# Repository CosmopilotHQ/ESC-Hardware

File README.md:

<p align="center">

</p>

# Brushed Speed Controller

This project aims to create a Brushed Electronic Speed Controller (ESC) using KiCad. The ESC is designed to control the speed of a brushed DC motor using pulse-width modulation (PWM) signals.

## Getting Started

To get started with this project, follow these steps:

1. Clone this repository to your local machine.
   ```bash
   git clone https://github.com/CosmopilotHQ/ESC-Hardware.git
   ```

## Port Manipulation

Port manipulation is a method used to directly control the state of GPIO (General Purpose Input/Output). Instead of using digitalWrite() and digitalRead() functions, which are higher-level abstractions, port manipulation accesses the hardware registers directly.

### Clearing a Bit in a Register

To clear a bit in a register, you typically perform a bitwise AND operation between the register and the complement of a bitmask that has the desired bit set.

```c
register &= ~(1 << bit_position);
```

### Setting a Bit in a Register

To set a bit in a register, you typically perform a bitwise OR operation between the register and a bitmask that has the desired bit set.

```c
register |= (1 << bit_position);
```

### Example

- Setting Pin as Output

  ```C
  DDRD |= (1 << PD5);
  ```

- Turning Pin High

  ```c
  PORTB |= (1 << PD5);
  ```

- Turning Pin Low
  ```c
  PORTB &= ~(1 << PD5);
  ```

## License

This project is licensed under CERN Open Hardware License. You can find more details in the [LICENSE](LICENSE) file.

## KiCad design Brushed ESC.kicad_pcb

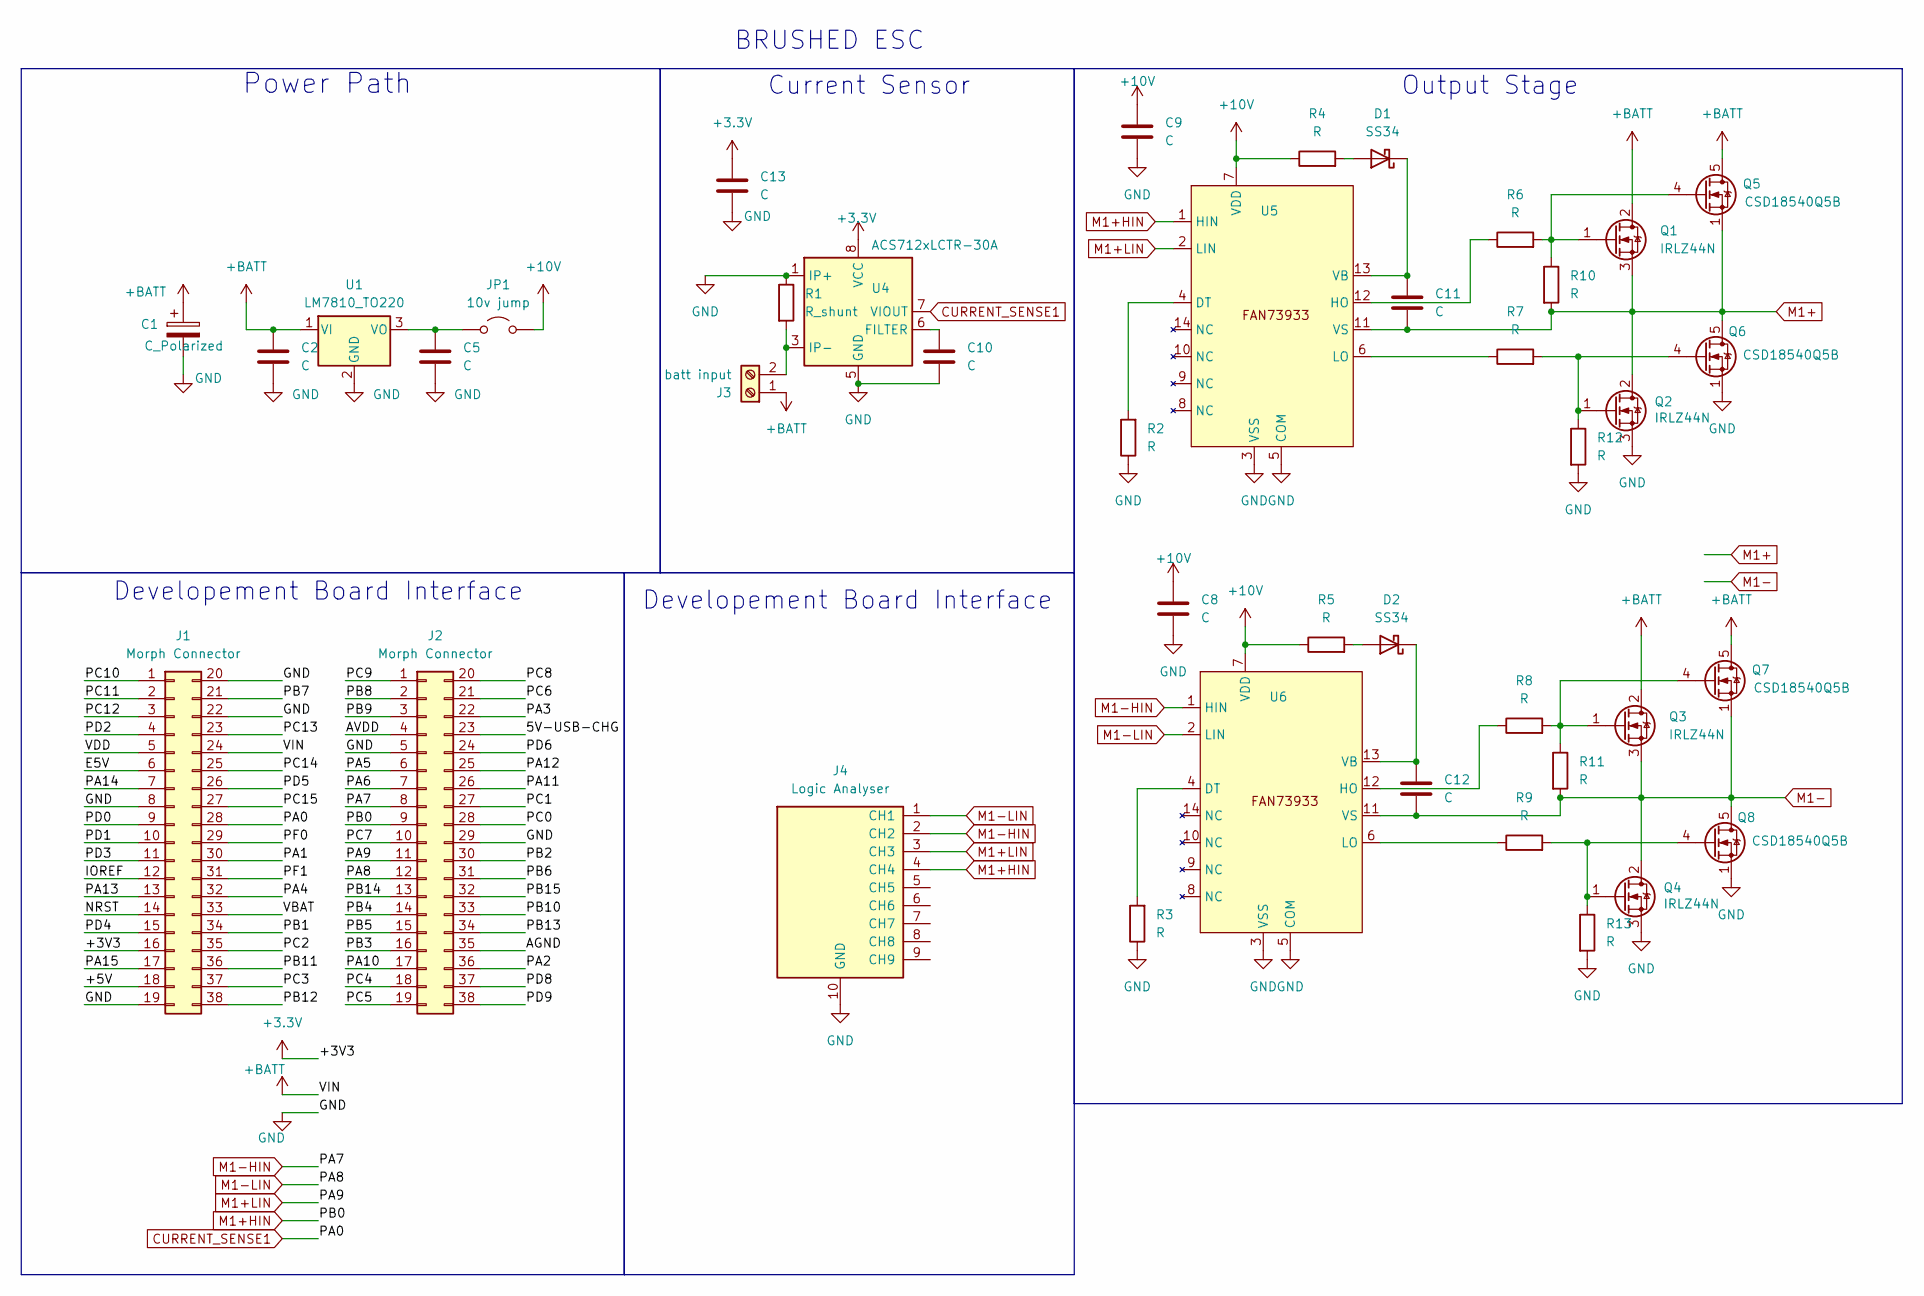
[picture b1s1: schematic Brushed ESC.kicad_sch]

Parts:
C1: C_Polarized; CP_Radial_D8.0mm_P5.00mm
C2, C5: C; C_1825_4564Metric_Pad1.57x6.80mm_HandSolder
C8, C9, C10, C11, C12: C; C_1206_3216Metric_Pad1.33x1.80mm_HandSolder
C13: C; C_1210_3225Metric_Pad1.33x2.70mm_HandSolder
D1, D2: SS34; D_SMA
J1, J2: Morph Connector; PinHeader_2x19_P2.54mm_Vertical
J3: batt input; JST_NV_B02P-NV_1x02_P5.00mm_Vertical
J4: Logic Analyser; IDC-Header_2x05_P2.54mm_Vertical
JP1: 10v jump; SolderJumper-2_P1.3mm_Open_TrianglePad1.0x1.5mm
Q1, Q2, Q3, Q4: IRLZ44N; TO-220-3_Vertical
Q5, Q6, Q7, Q8: CSD18540Q5B; Infineon_PG-TDSON-8_6.15x5.15mm
R1: R_shunt; R_2816_7142Metric_Pad3.20x4.45mm_HandSolder
R2, R3, R4, R5, R6, R7, R8, R9, R10, R11, R12, R13: R; R_1206_3216Metric_Pad1.30x1.75mm_HandSolder
U1: LM7810_TO220; TO-220-3_Vertical
U4: ACS712xLCTR-30A; SOIC-8_3.9x4.9mm_P1.27mm
U5, U6: SOIC-14_3.9x8.7mm_P1.27mm

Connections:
+3.3V: C13.1, J1.16, U4.8 (VCC)
+10V: C8.1, C9.1, JP1.2 (B), R4.1, R5.1, U5.7 (VDD), U6.7 (VDD)
+BATT: C1.1, C2.1, J1.24, J3.1, Q1.2 (D), Q3.2 (D), Q5.5 (D), Q7.5 (D), U1.1 (VI)
/5V-USB-CHG: J2.23
/+5V: J1.18
/AGND: J2.35
/AVDD: J2.4
/E5V: J1.6
/IOREF: J1.12
/NRST: J1.14
/PA1: J1.30
/PA2: J2.36
/PA3: J2.22
/PA4: J1.32
/PA5: J2.6
/PA6: J2.7
/PA10: J2.17
/PA11: J2.26
/PA12: J2.25
/PA13: J1.13
/PA14: J1.7
/PA15: J1.17
/PB1: J1.34
/PB2: J2.30
/PB3: J2.16
/PB4: J2.14
/PB5: J2.15
/PB6: J2.31
/PB7: J1.21
/PB8: J2.2
/PB9: J2.3
/PB10: J2.33
/PB11: J1.36
/PB12: J1.38
/PB13: J2.34
/PB14: J2.13
/PB15: J2.32
/PC0: J2.28
/PC1: J2.27
/PC2: J1.35
/PC3: J1.37
/PC4: J2.18
/PC5: J2.19
/PC6: J2.21
/PC7: J2.10
/PC8: J2.20
/PC9: J2.1
/PC10: J1.1
/PC11: J1.2
/PC12: J1.3
/PC13: J1.23
/PC14: J1.25
/PC15: J1.27
/PD0: J1.9
/PD1: J1.10
/PD2: J1.4
/PD3: J1.11
/PD4: J1.15
/PD5: J1.26
/PD6: J2.24
/PD8: J2.37
/PD9: J2.38
/PF0: J1.29
/PF1: J1.31
/VBAT: J1.33
/VDD: J1.5
CURRENT_SENSE1: J1.28, U4.7 (VIOUT)
GND: C1.2, C2.2, C5.2, C8.2, C9.2, C10.2, C13.2, J1.8, J1.19, J1.20, J1.22, J2.5, J2.29, J4.10 (GND), Q2.3 (S), Q4.3 (S), Q6.1 (S), Q6.2 (S), Q6.3 (S), Q8.1 (S), Q8.2 (S), Q8.3 (S), R1.1, R2.1, R3.1, R12.2, R13.2, U1.2 (GND), U4.1 (IP+), U4.2 (IP+), U4.5 (GND), U5.3 (VSS), U5.5 (COM), U6.3 (VSS), U6.5 (COM)
M1+: C11.2, Q1.3 (S), Q2.2 (D), Q5.1 (S), Q5.2 (S), Q5.3 (S), Q6.5 (D), R10.2, U5.11 (VS)
M1+HIN: J2.9, J4.4 (CH4), U5.1 (HIN)
M1+LIN: J2.11, J4.3 (CH3), U5.2 (LIN)
M1-: C12.2, Q3.3 (S), Q4.2 (D), Q7.1 (S), Q7.2 (S), Q7.3 (S), Q8.5 (D), R11.2, U6.11 (VS)
M1-HIN: J2.8, J4.2 (CH2), U6.1 (HIN)
M1-LIN: J2.12, J4.1 (CH1), U6.2 (LIN)
unnamed: D1.2 (A), R4.2
unnamed: C11.1, D1.1 (K), U5.13 (VB)
unnamed: D2.2 (A), R5.2
unnamed: C12.1, D2.1 (K), U6.13 (VB)
unnamed: J3.2, R1.2, U4.3 (IP-), U4.4 (IP-)
unnamed: C5.1, JP1.1 (A), U1.3 (VO)
unnamed: Q1.1 (G), Q5.4 (G), R6.2, R10.1
unnamed: Q2.1 (G), Q6.4 (G), R7.2, R12.1
unnamed: Q3.1 (G), Q7.4 (G), R8.2, R11.1
unnamed: Q4.1 (G), Q8.4 (G), R9.2, R13.1
unnamed: C10.1, U4.6 (FILTER)
unnamed: R2.2, U5.4 (DT)
unnamed: R6.1, U5.12 (HO)
unnamed: R7.1, U5.6 (LO)
unnamed: R3.2, U6.4 (DT)
unnamed: R8.1, U6.12 (HO)
unnamed: R9.1, U6.6 (LO)

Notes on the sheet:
BRUSHED ESC
Developement Board Interface
Output Stage
Power Path
Current Sensor

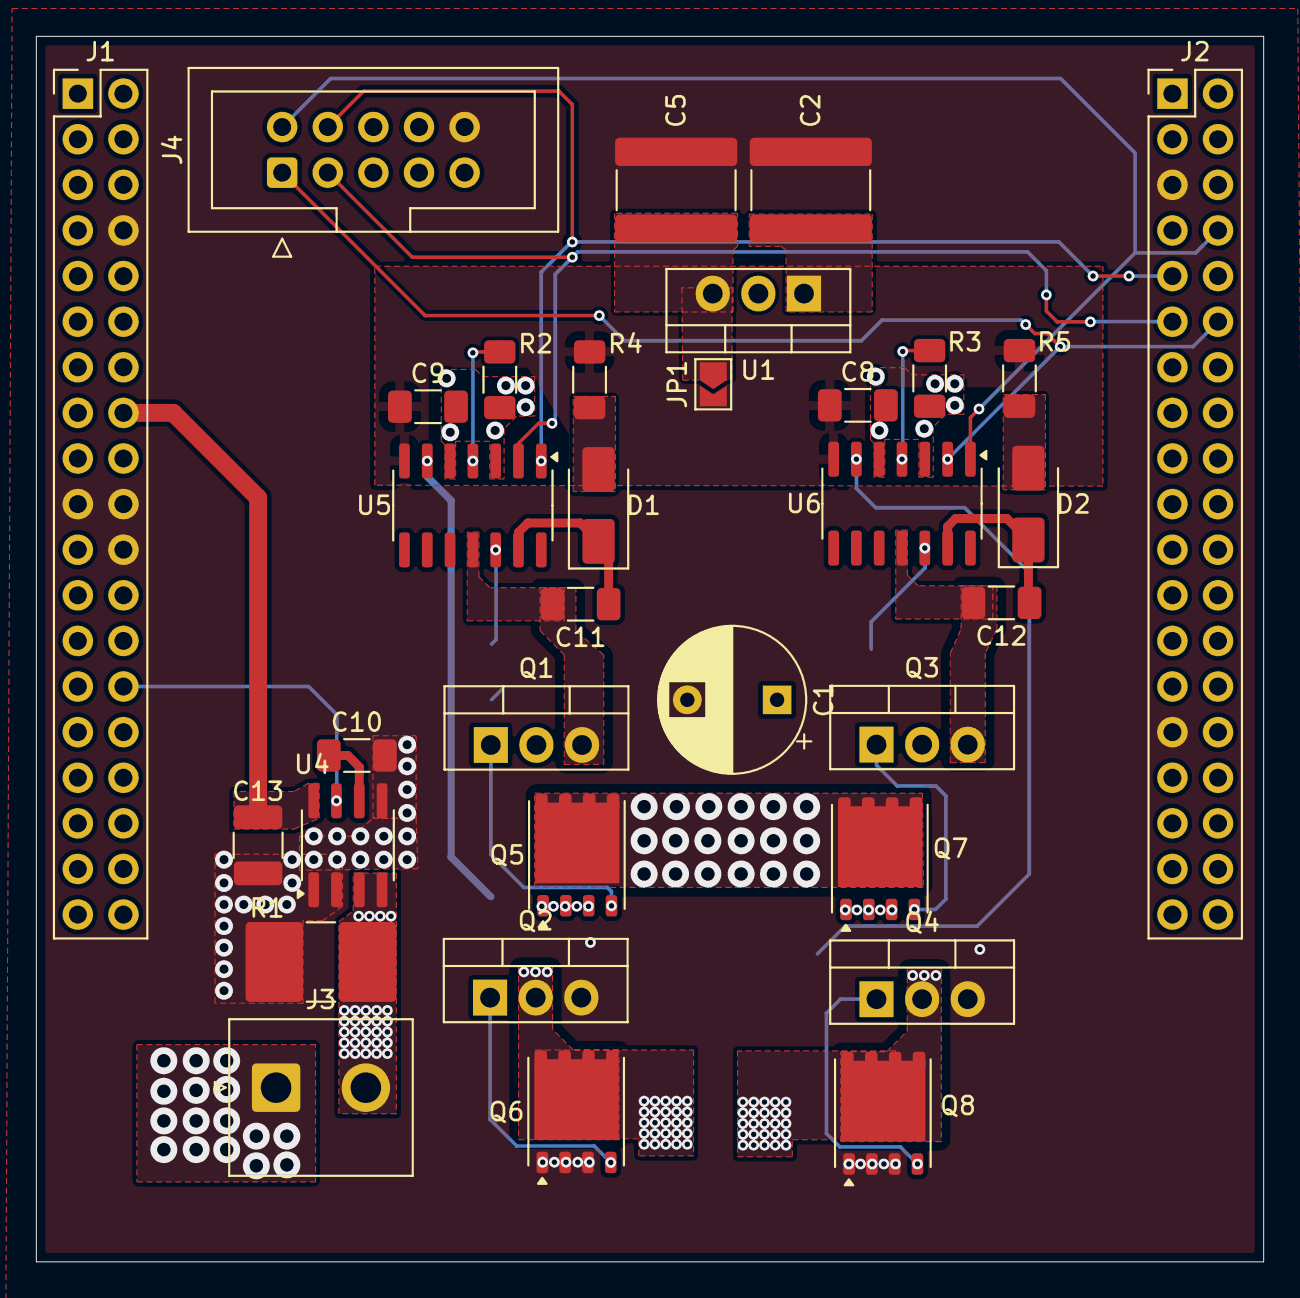
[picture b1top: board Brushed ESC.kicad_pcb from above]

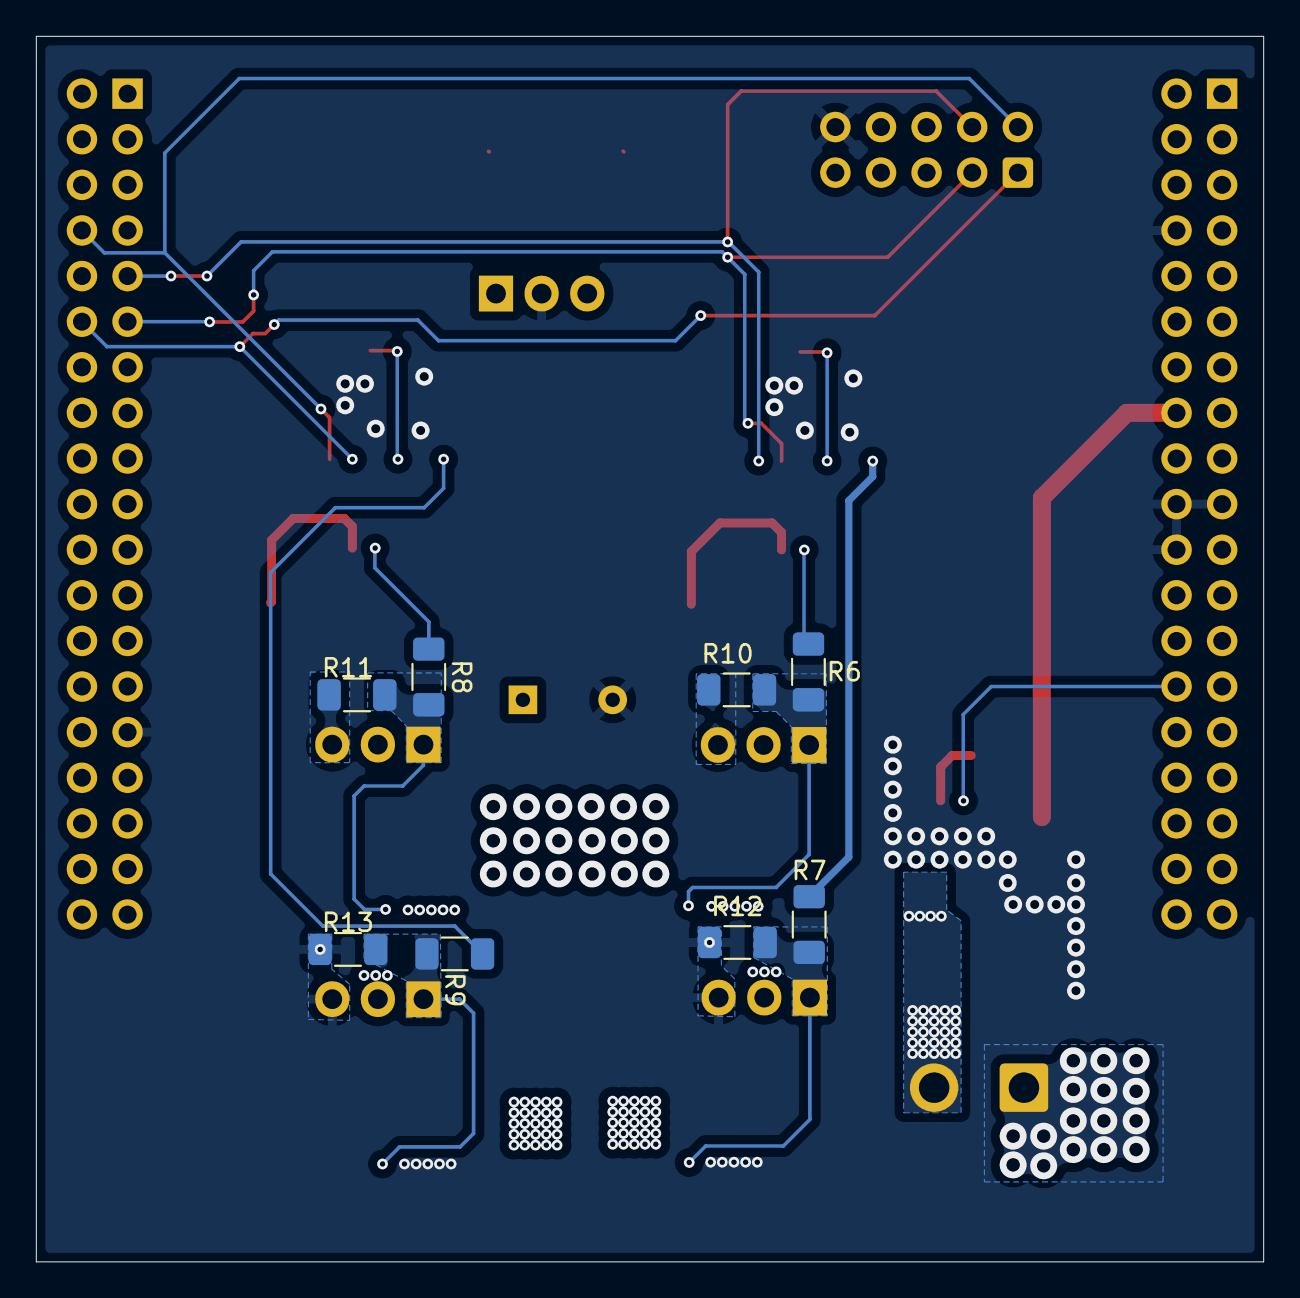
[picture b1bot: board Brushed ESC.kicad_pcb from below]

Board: 4 copper layers, 68.3 x 68.2 mm, 41 parts (8 on the bottom side), 28 nets.

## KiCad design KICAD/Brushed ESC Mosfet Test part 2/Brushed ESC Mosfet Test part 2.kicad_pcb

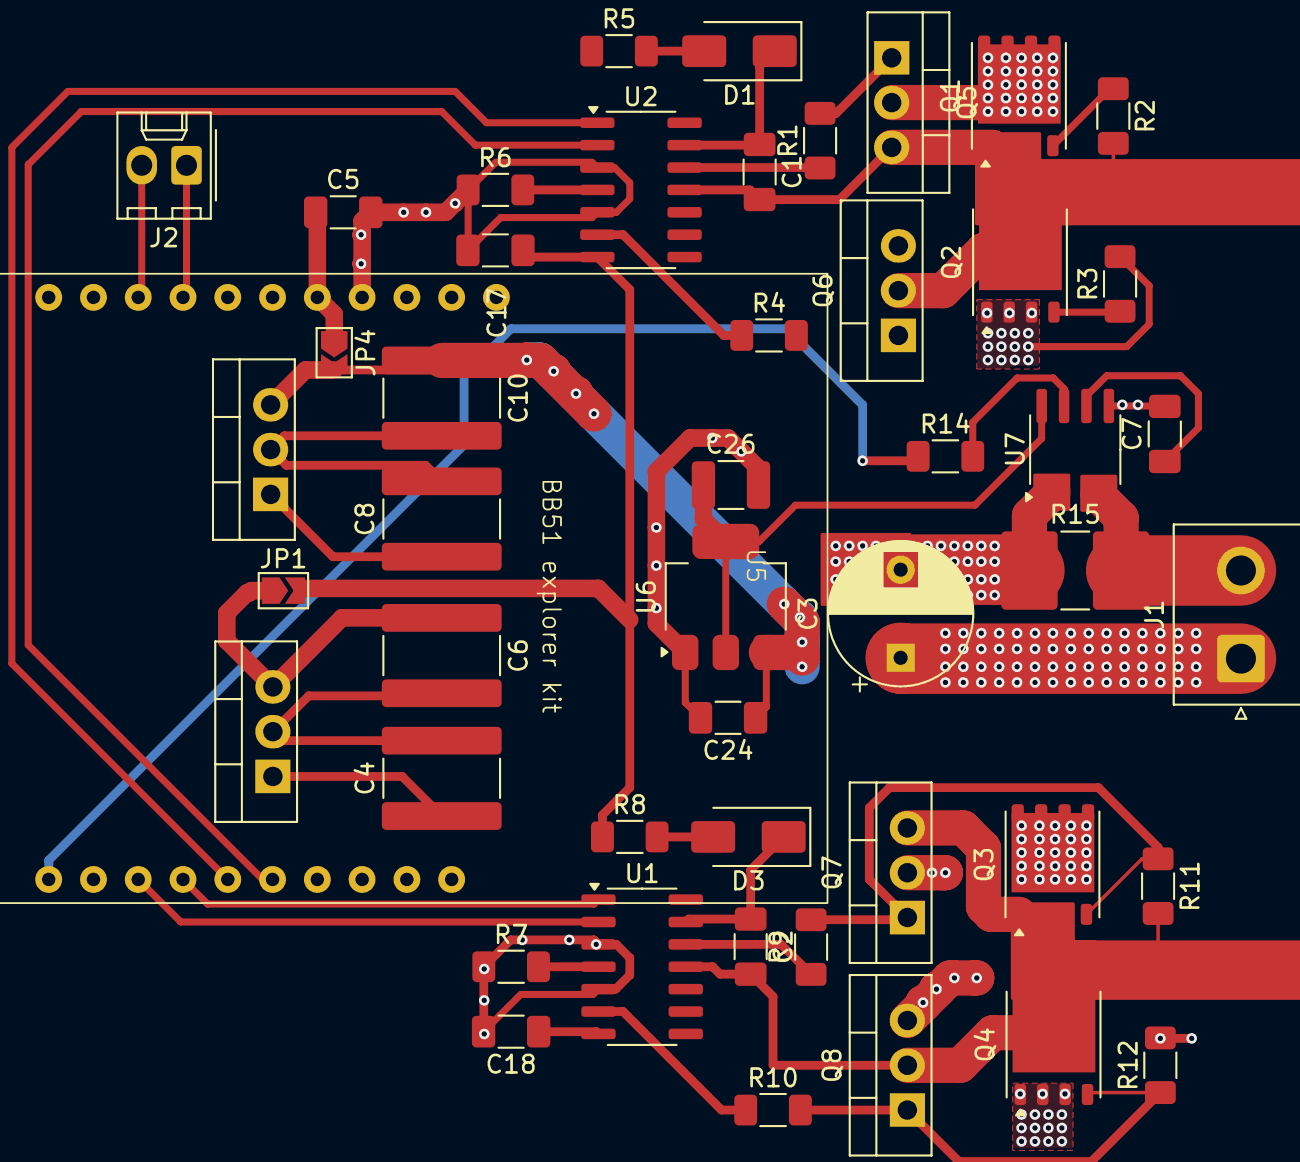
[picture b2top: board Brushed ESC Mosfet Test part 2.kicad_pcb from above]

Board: 4 copper layers, 48 parts (0 on the bottom side), 33 nets.

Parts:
C1, C2, C5, C7, C17, C18, C24: C; C_1206_3216Metric_Pad1.33x1.80mm_HandSolder
C3: C_Polarized; CP_Radial_D8.0mm_P5.00mm
C4, C6, C8, C10: C; C_1825_4564Metric_Pad1.57x6.80mm_HandSolder
C26: C; C_1210_3225Metric_Pad1.33x2.70mm_HandSolder
D1, D3: SS34; D_SMA
J1: batt input; JST_NV_B02P-NV_1x02_P5.00mm_Vertical
J2: Conn_01x02_Socket; Molex_KK-254_AE-6410-02A_1x02_P2.54mm_Vertical
JP1: 10v jump; SolderJumper-2_P1.3mm_Open_TrianglePad1.0x1.5mm
JP4: 5v batt jump to bb51; SolderJumper-2_P1.3mm_Open_TrianglePad1.0x1.5mm
Q1, Q2, Q3, Q4: CSD18540Q5B; Infineon_PG-TDSON-8_6.15x5.15mm
Q5, Q6, Q7, Q8: IRLZ44N; TO-220-3_Vertical
R1, R2, R3, R4, R5, R6, R7, R8, R9, R10, R11, R12, R14: R; R_1206_3216Metric_Pad1.30x1.75mm_HandSolder
R15: R_shunt; R_2816_7142Metric_Pad3.20x4.45mm_HandSolder
U1, U2: SOIC-14_3.9x8.7mm_P1.27mm
U3: LM7810_TO220; TO-220-3_Vertical
U4: LM7805_TO220; TO-220-3_Vertical
U5: BB51 EXPLORER KIT
U6: AMS1117-3.3; SOT-223-3_TabPin2
U7: ACS712xLCTR-30A; SOIC-8_3.9x4.9mm_P1.27mm

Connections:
5v_batt: C10.1, C24.1, JP4.2 (B), U4.3 (VO), U6.3 (VI)
+3.3V: C26.1, U6.2 (VO), U7.8 (VCC)
+10V: C17.1, C18.1, JP1.2 (B), R5.1, R8.1, U1.7 (VDD), U2.7 (VDD)
+BATT: C3.1, C4.1, C8.1, J1.1, Q1.5 (D), Q3.5 (D), Q5.2 (D), Q7.2 (D), U3.1 (VI), U4.1 (VI)
CURRENT_SENSE1: R14.2, U7.7 (VIOUT)
GND: C3.2, C4.2, C5.2, C6.2, C7.2, C8.2, C10.2, C17.2, C18.2, C24.2, C26.2, Q2.1 (S), Q2.2 (S), Q2.3 (S), Q4.1 (S), Q4.2 (S), Q4.3 (S), Q6.3 (S), Q8.3 (S), R3.2, R6.1, R7.1, R12.2, R15.1, U1.3 (VSS), U1.5 (COM), U2.3 (VSS), U2.5 (COM), U3.2 (GND), U4.2 (GND), U5.4 (GND), U5.19 (GND), U6.1 (GND), U7.1 (IP+), U7.2 (IP+), U7.5 (GND)
M1+: C1.2, Q1.1 (S), Q1.2 (S), Q1.3 (S), Q2.5 (D), Q5.3 (S), Q6.2 (D), R2.2, U2.11 (VS)
M1+HIN: U2.1 (HIN), U5.16 (P1.1)
M1+LIN: U2.2 (LIN), U5.17 (P1.2)
M1-: C2.2, Q3.1 (S), Q3.2 (S), Q3.3 (S), Q4.5 (D), Q7.3 (S), Q8.2 (D), R11.2, U1.11 (VS)
M1-HIN: U1.1 (HIN), U5.15 (P1.0)
M1-LIN: U1.2 (LIN), U5.14 (P1.3)
unnamed: D1.2 (A), R5.2
unnamed: C1.1, D1.1 (K), U2.13 (VB)
unnamed: D3.2 (A), R8.2
unnamed: C2.1, D3.1 (K), U1.13 (VB)
unnamed: J1.2, R15.2, U7.3 (IP-), U7.4 (IP-)
unnamed: C6.1, JP1.1 (A), U3.3 (VO)
unnamed: C5.1, JP4.1 (A), U5.5 (5v)
unnamed: Q1.4 (G), Q5.1 (G), R1.2, R2.1
unnamed: Q2.4 (G), Q6.1 (G), R3.1, R4.2
unnamed: Q3.4 (G), Q7.1 (G), R9.2, R11.1
unnamed: Q4.4 (G), Q8.1 (G), R10.2, R12.1
unnamed: R7.2, U1.4 (DT)
unnamed: R9.1, U1.12 (HO)
unnamed: R10.1, U1.6 (LO)
unnamed: R6.2, U2.4 (DT)
unnamed: R1.1, U2.12 (HO)
unnamed: R4.1, U2.6 (LO)
unnamed: R14.1, U5.12 (P0.3)
unnamed: C7.1, U7.6 (FILTER)
RX1: J2.2, U5.9 (P0.5)
TX1: J2.1, U5.8 (P0.4)

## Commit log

2024-12-15 Moved Code to another repo and cleaned this repo. Check changelog.md
2024-12-19 Cleaned the Repo structure
2024-12-26 Updated ESC schematic
2024-12-26 Layout done
2024-12-26 Changed Board from BB51 to STM32G0XX
2025-01-04 Pre-Alpha PCB Layout
2025-01-06 Pre-Alpha PCB Layout V2
2025-01-07 New Branch for final PCB
2025-01-08 Update LICENSE
2025-01-09 Changed Resistor Footprints
2025-01-12 Added: Voltage Regulator
2025-01-12 Added: Component Values for Voltage Regualtors
2025-01-15 Added: Current Sense Circuit
2025-01-15 Updated To-Do List
2025-01-16 Updated BOM
2025-01-25 Added: 3D Model for components
2025-03-09 Added: Build Pipeline - Nightly build and prodcution build
2025-03-09 Updated: Kicad version from v8 to v9
2025-03-09 Fixed: Project name in Build Pipeline
2025-03-29 Added: Issue Form
2025-03-29 Fixed: #2
